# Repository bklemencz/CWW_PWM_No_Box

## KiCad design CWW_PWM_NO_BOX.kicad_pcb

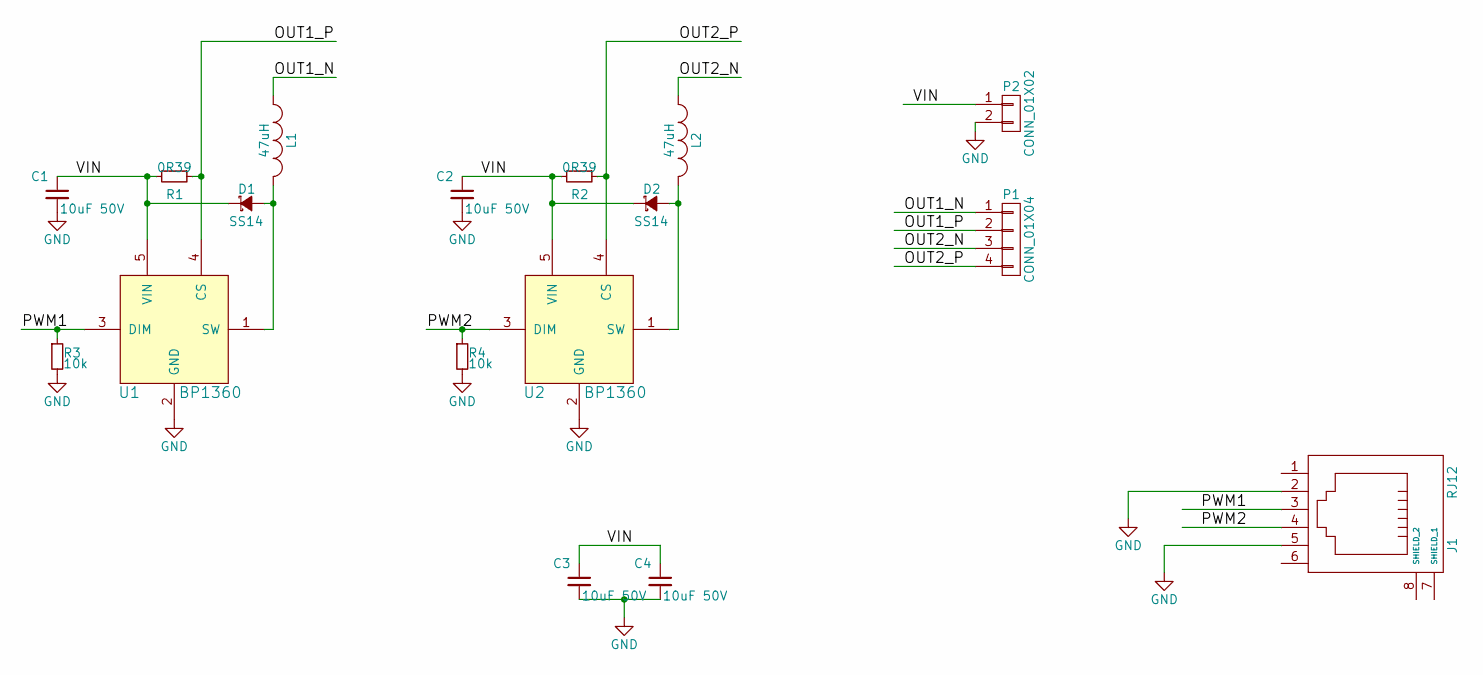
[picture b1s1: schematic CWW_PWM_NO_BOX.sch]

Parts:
C1, C2, C3, C4: 10uF 50V; C_1206
D1, D2: SS14; SMA_Standard
J1: RJ12; RJ12_2mm_Pitch
L1, L2: 47uH; IND_SMD_CD43
P1: CONN_01X04; Pin_Header_Straight_1x04
P2: CONN_01X02; Pin_Header_Straight_1x02
R1, R2: 0R39; R_1206
R3, R4: 10k; R_0805
U1, U2: BP1360; SOT-23-5

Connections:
/OUT1_N: L1.1, P1.1
/OUT1_P: P1.2, R1.1, U1.4 (CS)
/OUT2_N: L2.1, P1.3
/OUT2_P: P1.4, R2.1, U2.4 (CS)
/PWM1: J1.3, R3.1, U1.3 (DIM)
/PWM2: J1.4, R4.1, U2.3 (DIM)
/VIN: C1.1, C2.1, C3.1, C4.1, D1.1 (K), D2.1 (K), P2.1, R1.2, R2.2, U1.5 (VIN), U2.5 (VIN)
GND: C1.2, C2.2, C3.2, C4.2, J1.2, J1.5, P2.2, R3.2, R4.2, U1.2 (GND), U2.2 (GND)
unnamed: D1.2 (A), L1.2, U1.1 (SW)
unnamed: D2.2 (A), L2.2, U2.1 (SW)

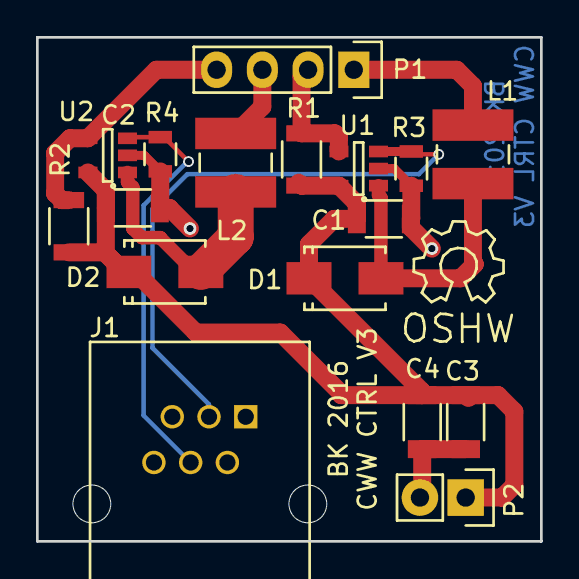
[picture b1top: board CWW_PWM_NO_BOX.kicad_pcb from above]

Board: 2 copper layers, 28.0 x 28.0 mm, 17 parts (0 on the bottom side), 10 nets.

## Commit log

2016-03-15 :octocat: Added .gitattributes & .gitignore files
2016-03-15 Initial
2016-03-15 PCB Change
2016-03-16 go back
2016-03-17 rj12 change
2016-03-23 gerber
